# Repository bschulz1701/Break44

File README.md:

# Break44
A collection of various breakout and other utility boards

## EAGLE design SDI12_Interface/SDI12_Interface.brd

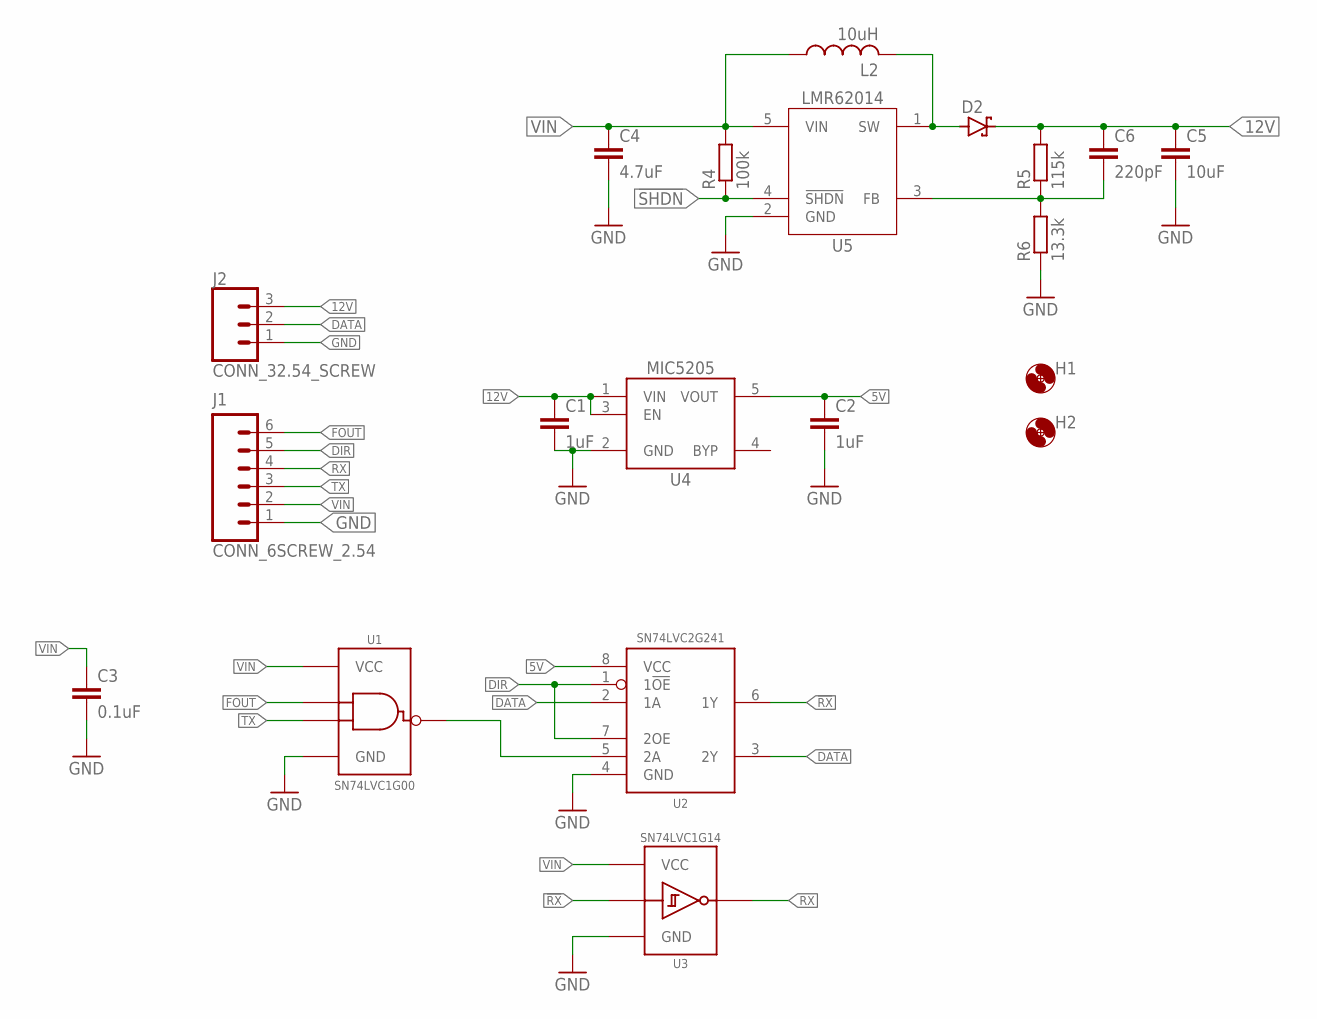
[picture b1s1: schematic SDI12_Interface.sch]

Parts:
C1, C2: 1uF; C0603
C3: 0.1uF; C0603
C4: 4.7uF; C0805
C5: 10uF; C0805; MPN TMK212BBJ106KG-T; DIGIKEY 587-2985-1-ND
C6: 220pF; C0603
D2: DIODE_SCHOTTKYSOD-123; SOD-123; MPN MBR0520LT1G; DIGIKEY MBR0520LT1GOSCT-ND
H1, H2: MOUNTING_HOLE2_NP; 2_56
J1: CONN_6SCREW_2.54; 1X06_SCREW
J2: CONN_32.54_SCREW; 1X03_SCREW
L2: 10uH; 1008; MPN 74438323100; DIGIKEY 732-4851-1-ND
R4: 100k; R0603
R5: 115k; R0603
R6: 13.3k; R0603
U1: SN74LVC1G00SC70; DCK_R-PDSO-G5
U2: SN74LVC2G241DCU; DCU_(R-PDSO-G8)
U3: SN74LVC1G14DCK; DCK_R-PDSO-G5
U4: MIC5205_5V; SOT23-5
U5: LMR62014SOT23; DBV0005A

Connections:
5V: C2.1, U2.8 (VCC), U4.5 (VOUT)
12V: C1.1, C5.1, C6.1, D2.CAT (C), J2.3, R5.2, U4.1 (VIN), U4.3 (EN)
!RX: U2.6 (1Y), U3.2 (A)
!SHDN: R4.1, U5.4 (!SHDN)
BYP: U4.4 (BYP)
DATA: J2.2, U2.2 (1A), U2.3 (2Y)
DIR: J1.5, U2.1 (1!OE), U2.7 (2OE)
FOUT: J1.6, U1.1 (A)
GND: C1.2, C2.2, C3.2, C4.2, C5.2, J1.1, J2.1, R6.1, U1.3 (GND), U2.4 (GND), U3.3 (GND), U4.2 (GND), U5.2 (GND)
unnamed: U1.4 (Y), U2.5 (2A)
unnamed: C6.2, R5.1, R6.2, U5.3 (FB)
RX: J1.4, U3.4 (Y)
SW1: D2.ANODE (A), L2.2, U5.1 (SW)
TX: J1.3, U1.2 (B)
VIN: C3.1, C4.1, J1.2, L2.1, R4.2, U1.5 (VCC), U3.5 (VCC), U5.5 (VIN)

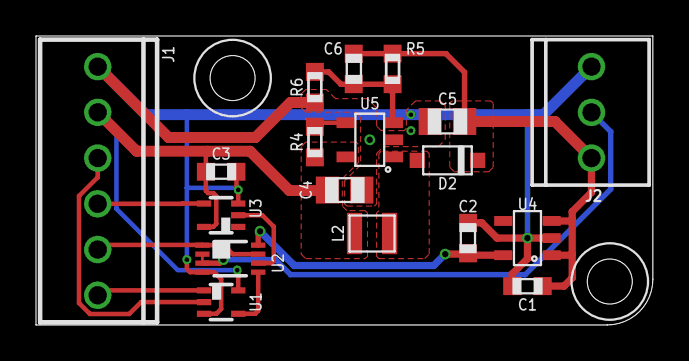
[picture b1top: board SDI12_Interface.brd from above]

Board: 2 copper layers, 34.3 x 16.1 mm, 20 parts (0 on the bottom side), 14 nets.

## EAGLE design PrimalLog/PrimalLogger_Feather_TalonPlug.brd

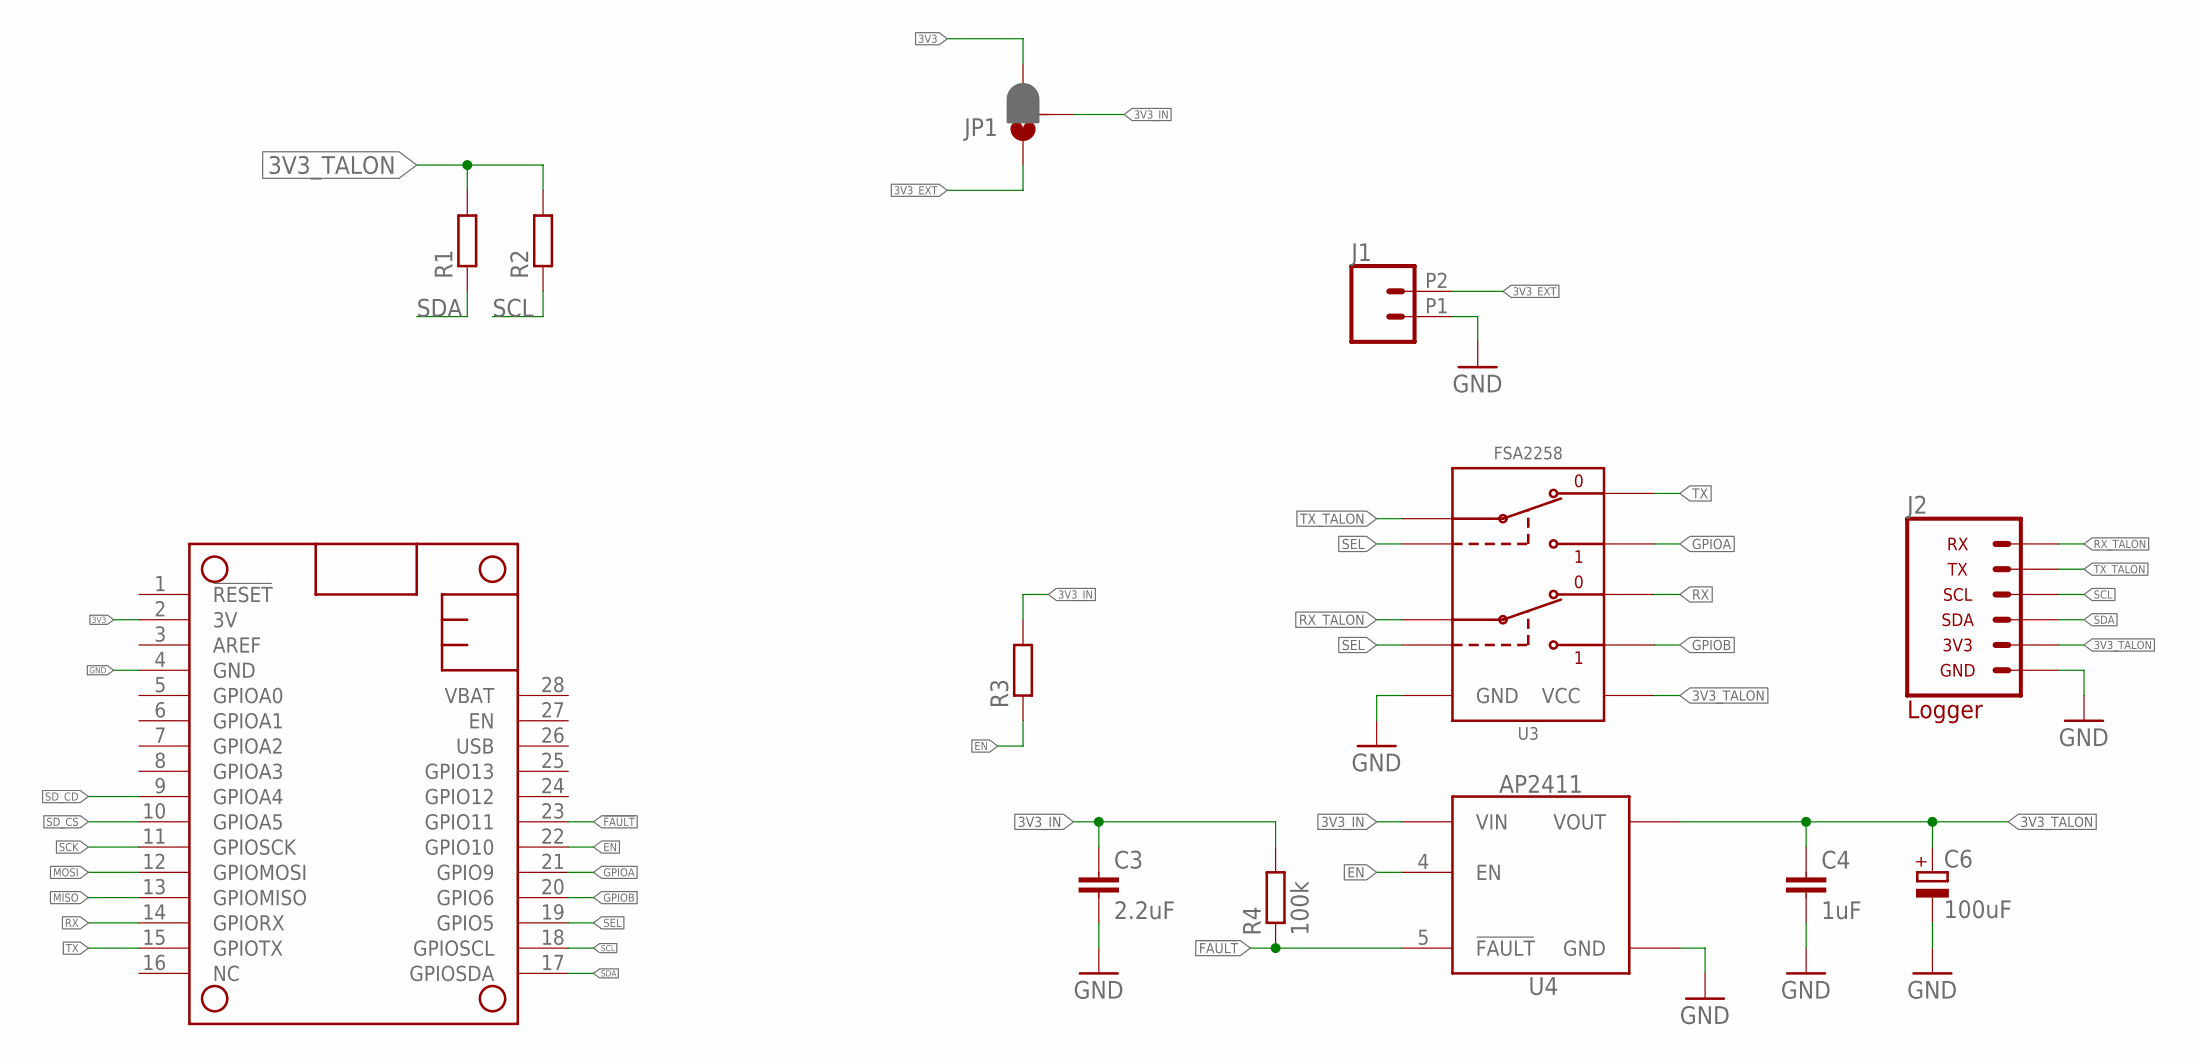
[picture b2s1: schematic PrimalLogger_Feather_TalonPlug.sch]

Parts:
C3: 2.2uF; C0603
C4: 1uF; C0603
C6: 100uF; C1411_TANT; MPN TPSB107M010R0400; DIGIKEY 478-5231-1-ND
J1: CONN_022.54_SCREW_ROUND; 1X02_2.54_SCREWTERM_ROUND
J2: CONN_TALON_LOGGER; 1X06_MICROLOCKPLUS_RT
JP1: JUMPER-SMT_3_1-NC_PASTE_SILK; SMT-JUMPER_3_1-NC_PASTE_SILK
MS1: FEATHERWING_NODIM; FEATHERWING_DIM
R1, R2: R-EU_10KR0603; R0603
R3: R-EU_100KR0603; R0603
R4: 100k; R0603
U3: FSA2258; MICROPAK_10
U4: AP2411; MSOP_8EP

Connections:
3V3: JP1.3, MS1.2 (3V)
3V3_EXT: J1.P2 (2), JP1.1
3V3_IN: C3.1, JP1.2, R3.2, R4.2, U4.2 (VIN), U4.3 (VIN)
3V3_TALON: C4.1, C6.ANODE (+), J2.2 (3V3), R1.2, R2.2, U3.10 (VCC), U4.6 (VOUT), U4.7 (VOUT)
!FAULT: MS1.23 (GPIO11), R4.1, U4.5 (!FAULT)
EN: MS1.22 (GPIO10), R3.1, U4.4 (EN)
GND: C3.2, C4.2, C6.CATHODE (-), J1.P1 (1), J2.1 (GND), MS1.4 (GND), U3.5 (GND), U4.1 (GND), U4.EP (GND)
GPIOA: MS1.21 (GPIO9), U3.2 (1B1)
GPIOB: MS1.20 (GPIO6), U3.4 (2B1)
MISO: MS1.13 (GPIOMISO)
MOSI: MS1.12 (GPIOMOSI)
RX: MS1.14 (GPIORX), U3.3 (2B0)
RX_TALON: J2.6 (RX), U3.6 (2A)
SCK: MS1.11 (GPIOSCK)
SCL: J2.4 (SCL), MS1.18 (GPIOSCL), R2.1
SDA: J2.3 (SDA), MS1.17 (GPIOSDA), R1.1
SD_CD: MS1.9 (GPIOA4)
SD_CS: MS1.10 (GPIOA5)
SEL: MS1.19 (GPIO5), U3.7 (S2), U3.8 (S1)
TX: MS1.15 (GPIOTX), U3.1 (1B0)
TX_TALON: J2.5 (TX), U3.9 (1A)

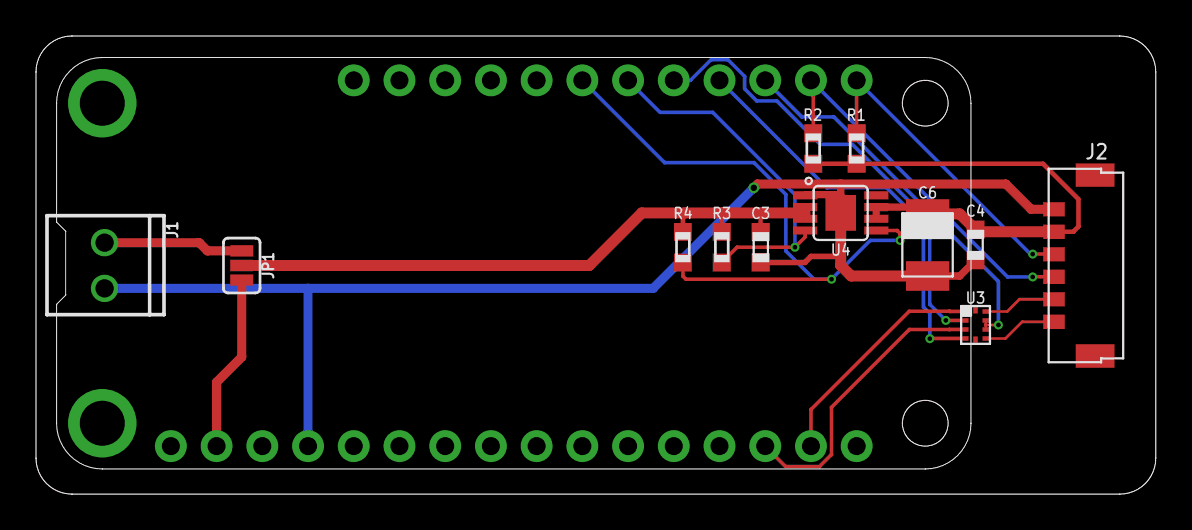
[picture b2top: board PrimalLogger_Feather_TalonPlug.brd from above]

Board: 2 copper layers, 62.2 x 25.5 mm, 13 parts (0 on the bottom side), 16 nets.

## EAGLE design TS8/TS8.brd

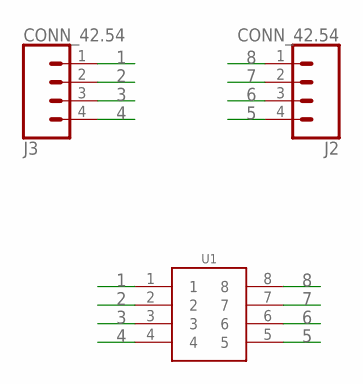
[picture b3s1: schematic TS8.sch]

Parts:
J2, J3: CONN_42.54; 1X04
U1: GEN_8TS8; TS8

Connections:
1: J3.1, U1.1
2: J3.2, U1.2
3: J3.3, U1.3
4: J3.4, U1.4
5: J2.4, U1.5
6: J2.3, U1.6
7: J2.2, U1.7
8: J2.1, U1.8

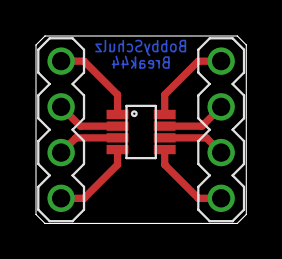
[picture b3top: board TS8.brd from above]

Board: 2 copper layers, 11.7 x 10.4 mm, 3 parts (0 on the bottom side), 8 nets.

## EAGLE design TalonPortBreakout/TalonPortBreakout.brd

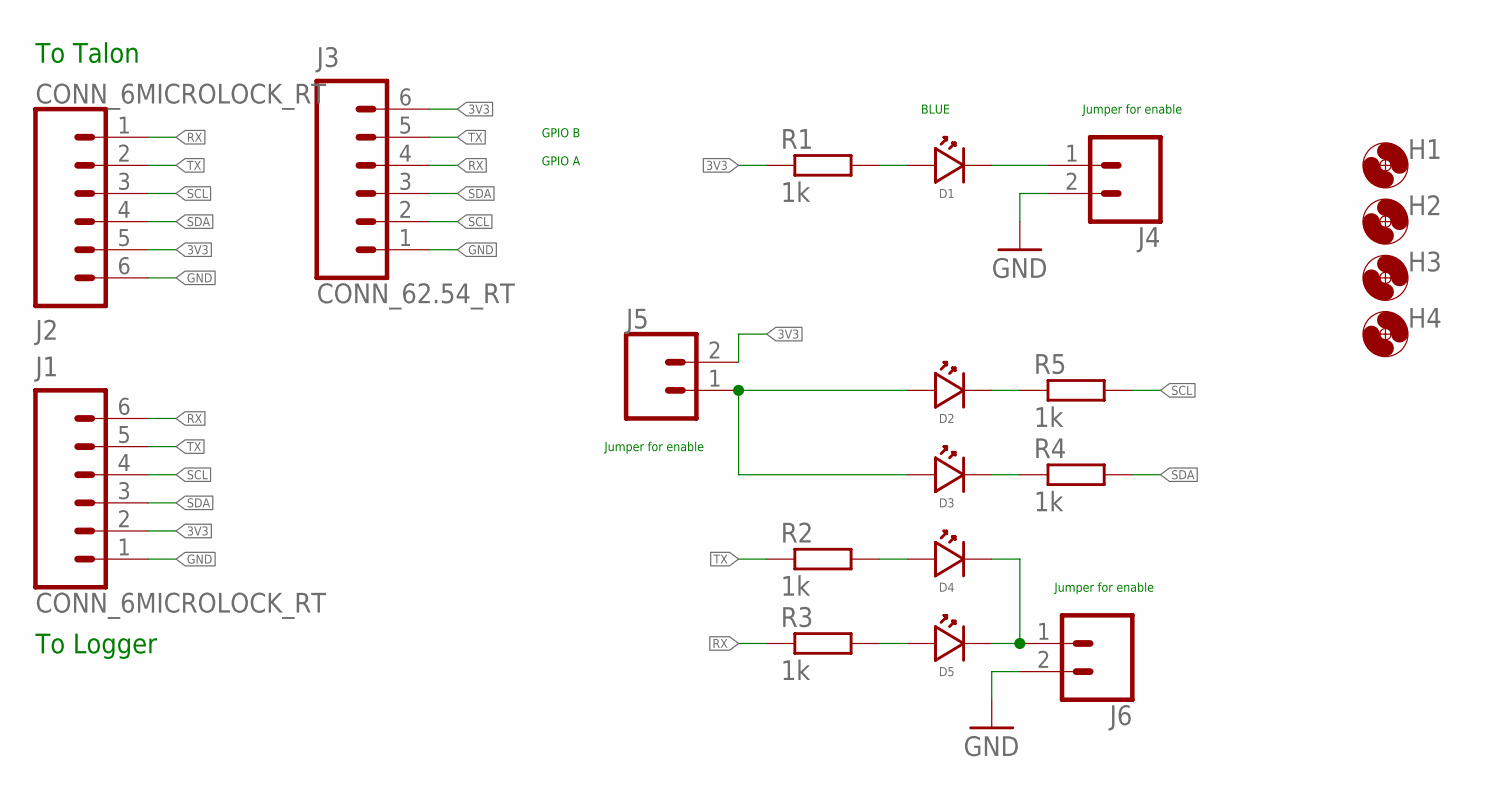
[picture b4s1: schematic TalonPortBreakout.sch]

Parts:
D1: LEDBLUE0603; LED_0603
D2, D3: LEDAMBER0603; LED_0603
D4: LEDGREEN0603; LED_0603
D5: LEDRED0603; LED_0603
H1, H2, H3, H4: MOUNTING_HOLE2_NP; 2_56
J1, J2: CONN_6MICROLOCK_RT; 1X06_MICROLOCKPLUS_RT
J3: CONN_62.54_RT; 1X06/90
J4, J5, J6: CONN_02; 1X02
R1, R2, R3, R4, R5: 1k; R0402

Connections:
3V3: J1.2, J2.5, J3.6, J5.2, R1.1
GND: J1.1, J2.6, J3.1, J4.2, J6.2
unnamed: D1.ANODE, R1.2
unnamed: D1.CATHODE, J4.1
unnamed: D4.ANODE, R2.2
unnamed: D5.ANODE, R3.2
unnamed: D3.CATHODE, R4.1
unnamed: D2.CATHODE, R5.1
unnamed: D4.CATHODE, D5.CATHODE, J6.1
unnamed: D2.ANODE, D3.ANODE, J5.1
RX: J1.6, J2.1, J3.4, R3.1
SCL: J1.4, J2.3, J3.2, R5.2
SDA: J1.3, J2.4, J3.3, R4.2
TX: J1.5, J2.2, J3.5, R2.1

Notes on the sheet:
GPIO B
GPIO A
BLUE
Jumper for enable
To Talon
To Logger

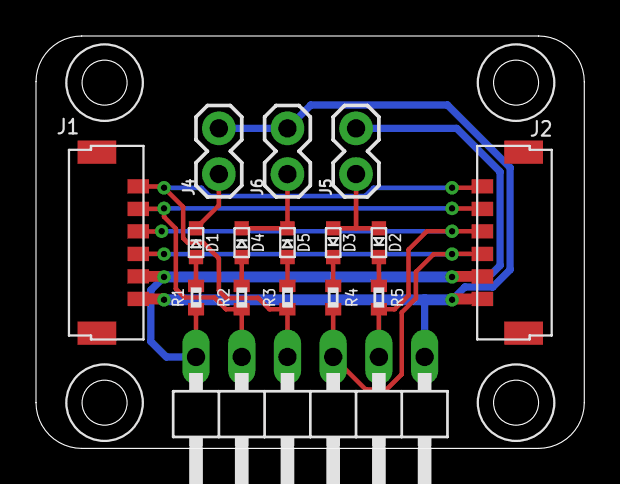
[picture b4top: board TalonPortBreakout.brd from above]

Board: 2 copper layers, 30.5 x 22.9 mm, 20 parts (0 on the bottom side), 14 nets.

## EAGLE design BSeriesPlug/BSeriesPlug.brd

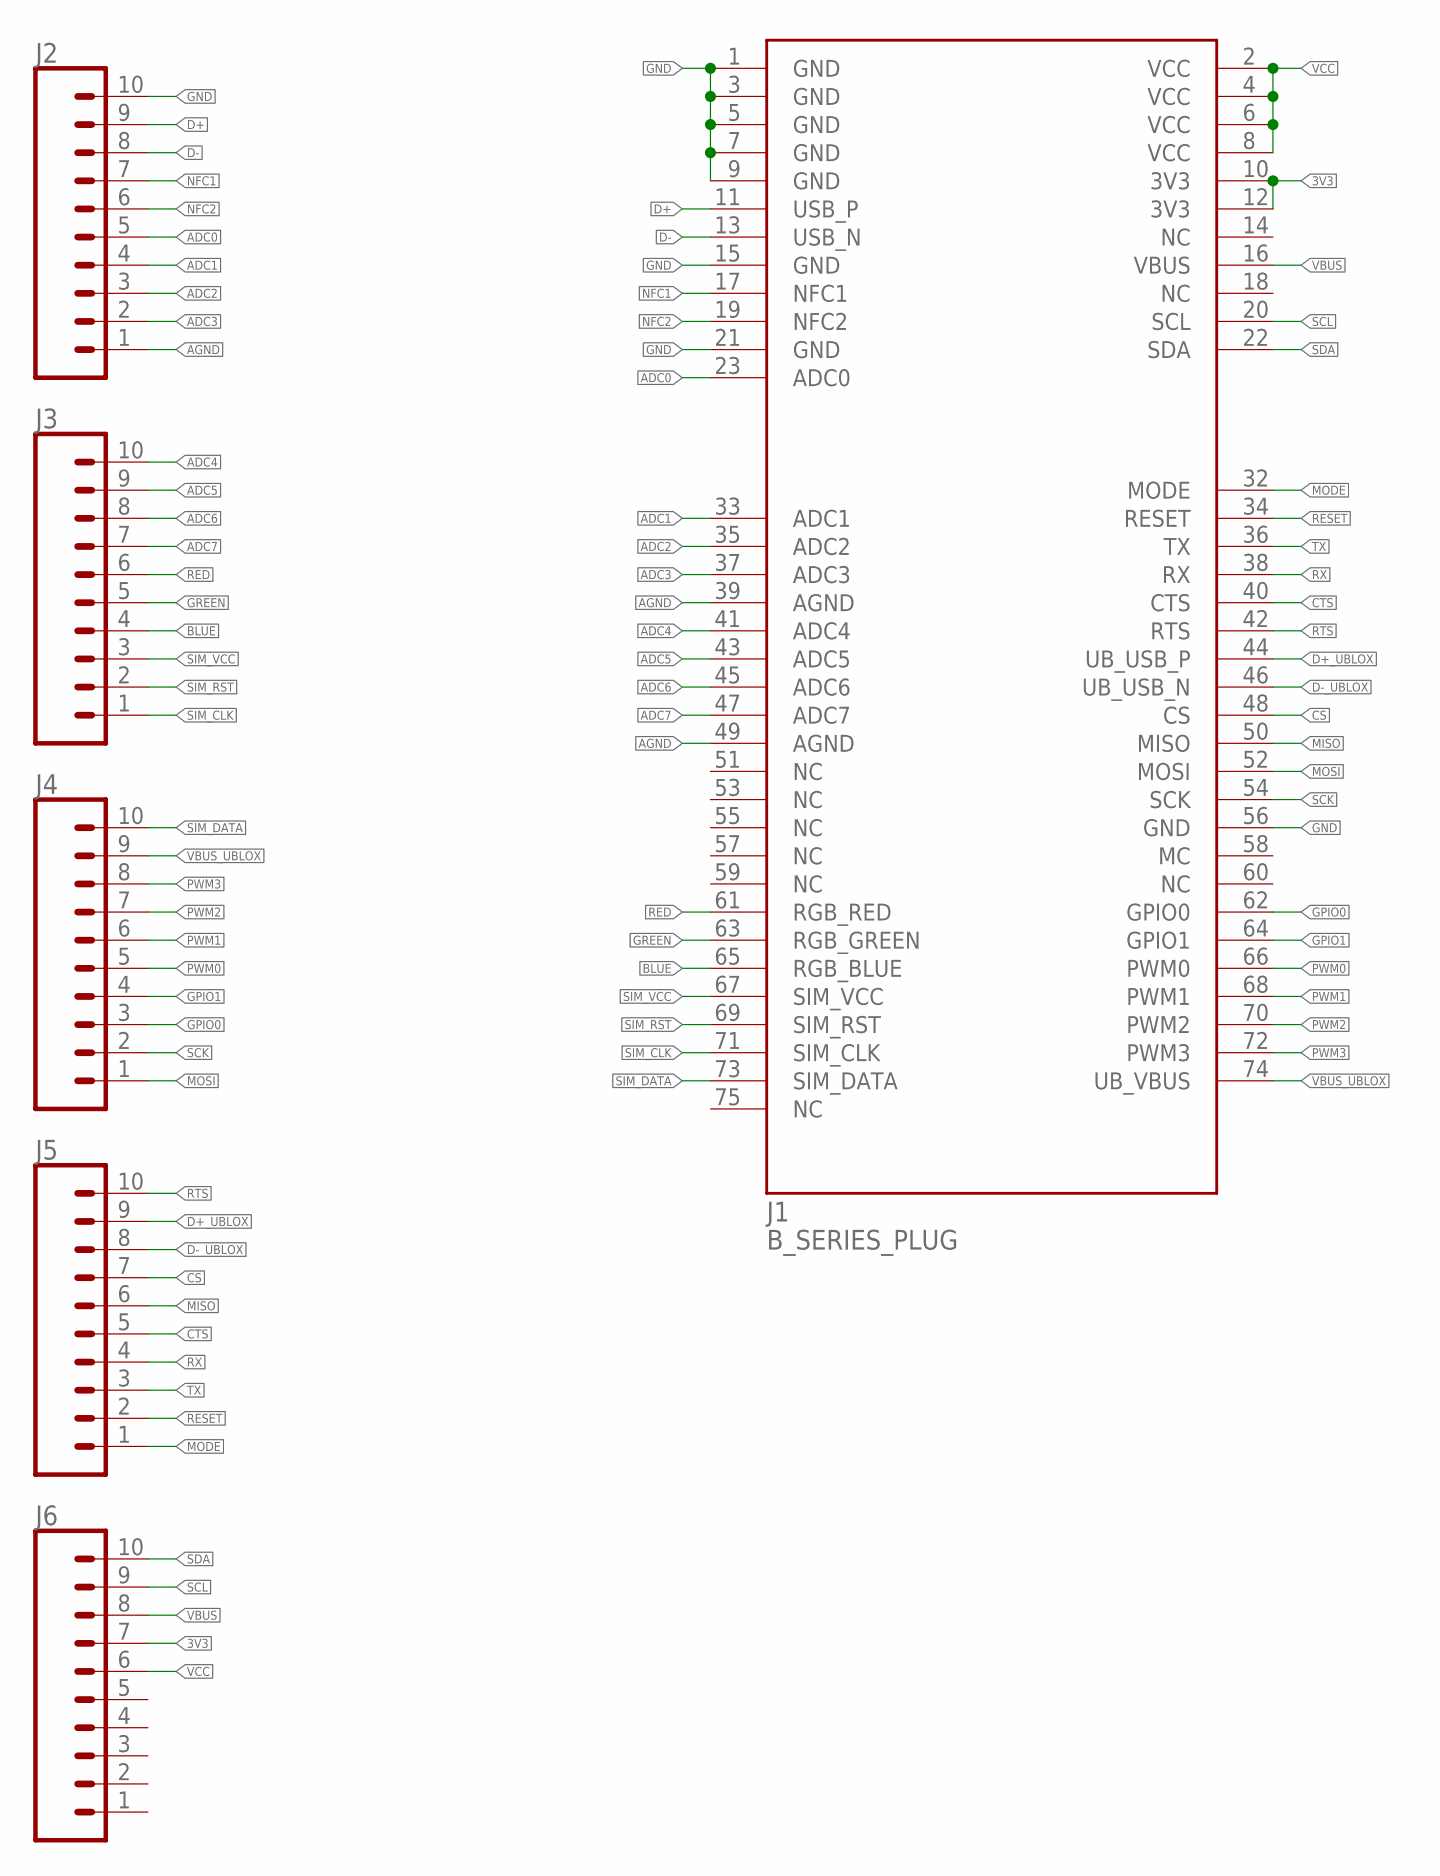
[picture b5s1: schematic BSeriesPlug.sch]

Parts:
J1: B_SERIES_PLUG; M.2-CARD-E-22
J2, J3, J4, J5, J6: CONN_10"; 1X10

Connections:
3V3: J1.10 (3V3), J1.12 (3V3), J6.7
ADC0: J1.23 (ADC0), J2.5
ADC1: J1.33 (ADC1), J2.4
ADC2: J1.35 (ADC2), J2.3
ADC3: J1.37 (ADC3), J2.2
ADC4: J1.41 (ADC4), J3.10
ADC5: J1.43 (ADC5), J3.9
ADC6: J1.45 (ADC6), J3.8
ADC7: J1.47 (ADC7), J3.7
AGND: J1.39 (AGND), J1.49 (AGND), J2.1
BLUE: J1.65 (RGB_BLUE), J3.4
CS: J1.48 (CS), J5.7
CTS: J1.40 (CTS), J5.5
D+: J1.11 (USB_P), J2.9
D+_UBLOX: J1.44 (UB_USB_P), J5.9
D-: J1.13 (USB_N), J2.8
D-_UBLOX: J1.46 (UB_USB_N), J5.8
GND: J1.1 (GND), J1.3 (GND), J1.5 (GND), J1.7 (GND), J1.9 (GND), J1.15 (GND), J1.21 (GND), J1.56 (GND), J2.10
GPIO0: J1.62 (GPIO0), J4.3
GPIO1: J1.64 (GPIO1), J4.4
GREEN: J1.63 (RGB_GREEN), J3.5
MISO: J1.50 (MISO), J5.6
MODE: J1.32 (MODE), J5.1
MOSI: J1.52 (MOSI), J4.1
NFC1: J1.17 (NFC1), J2.7
NFC2: J1.19 (NFC2), J2.6
PWM0: J1.66 (PWM0), J4.5
PWM1: J1.68 (PWM1), J4.6
PWM2: J1.70 (PWM2), J4.7
PWM3: J1.72 (PWM3), J4.8
RED: J1.61 (RGB_RED), J3.6
RESET: J1.34 (RESET), J5.2
RTS: J1.42 (RTS), J5.10
RX: J1.38 (RX), J5.4
SCK: J1.54 (SCK), J4.2
SCL: J1.20 (SCL), J6.9
SDA: J1.22 (SDA), J6.10
SIM_CLK: J1.71 (SIM_CLK), J3.1
SIM_DATA: J1.73 (SIM_DATA), J4.10
SIM_RST: J1.69 (SIM_RST), J3.2
SIM_VCC: J1.67 (SIM_VCC), J3.3
TX: J1.36 (TX), J5.3
VBUS: J1.16 (VBUS), J6.8
VBUS_UBLOX: J1.74 (UB_VBUS), J4.9
VCC: J1.2 (VCC), J1.4 (VCC), J1.6 (VCC), J1.8 (VCC), J6.6

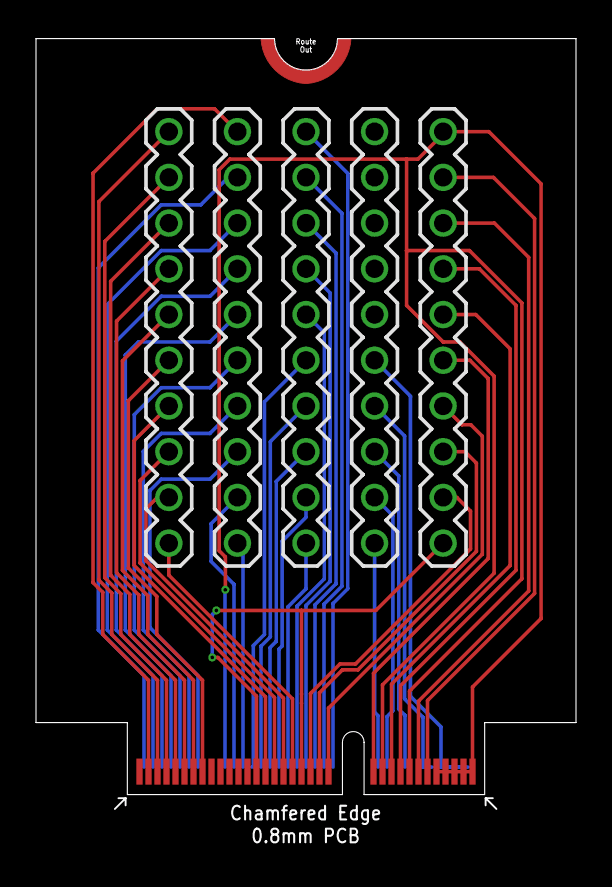
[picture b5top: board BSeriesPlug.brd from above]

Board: 2 copper layers, 29.9 x 45.2 mm, 6 parts (0 on the bottom side), 45 nets.

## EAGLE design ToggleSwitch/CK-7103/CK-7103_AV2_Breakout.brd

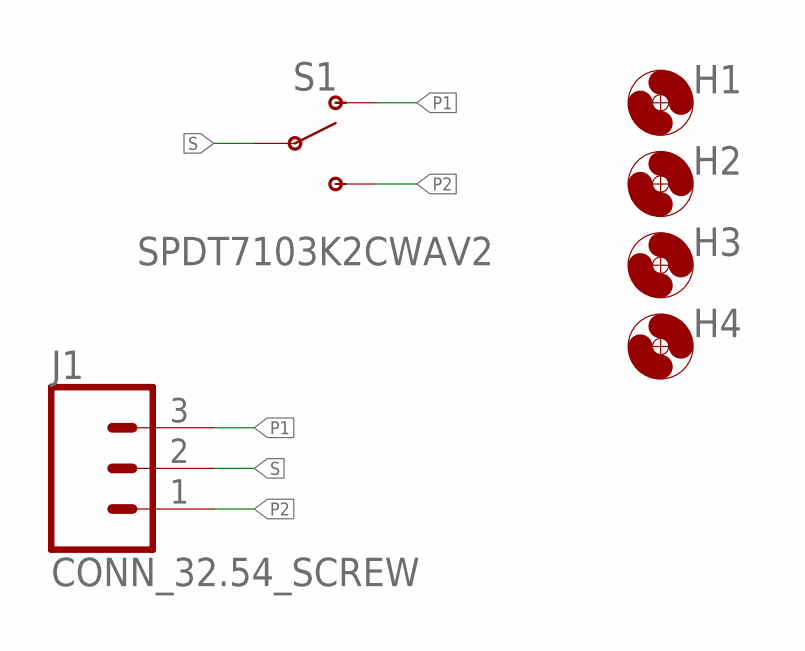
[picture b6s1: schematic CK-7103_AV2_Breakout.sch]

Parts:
H1, H2, H3, H4: MOUNTING_HOLE4_NP; 4_40
J1: CONN_32.54_SCREW; 1X03_SCREW
S1: SPDT7103K2CWAV2; 7103K2CWAV2

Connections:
P1: J1.3, S1.1 (O)
P2: J1.1, S1.3 (S)
S: J1.2, S1.2

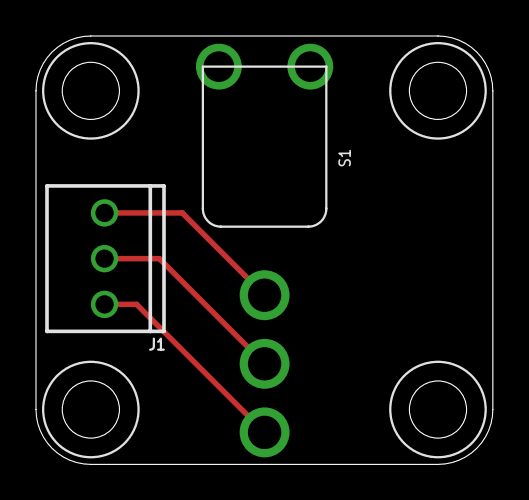
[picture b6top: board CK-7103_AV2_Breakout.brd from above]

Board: 2 copper layers, 25.4 x 23.8 mm, 6 parts (0 on the bottom side), 3 nets.

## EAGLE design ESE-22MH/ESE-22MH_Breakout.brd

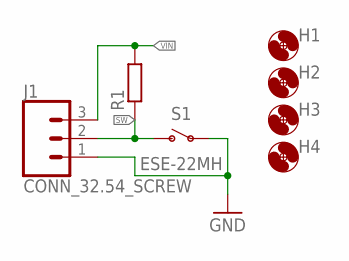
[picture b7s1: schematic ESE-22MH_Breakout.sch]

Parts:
H1, H2, H3, H4: MOUNTING_HOLE4_NP; 4_40
J1: CONN_32.54_SCREW; 1X03_SCREW
R1: R-EU_R0603; R0603
S1: ESE-22MH

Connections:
GND: J1.1, S1.2
SW: J1.2, R1.1, S1.1 (O)
VIN: J1.3, R1.2

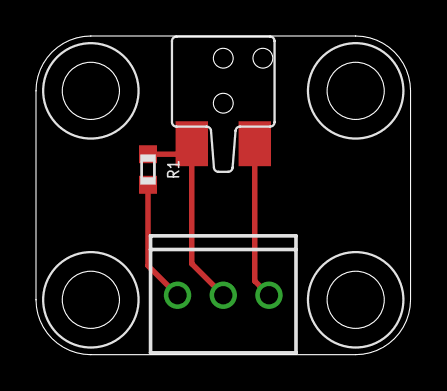
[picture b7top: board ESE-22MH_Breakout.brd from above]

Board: 2 copper layers, 20.8 x 17.7 mm, 7 parts (0 on the bottom side), 3 nets.

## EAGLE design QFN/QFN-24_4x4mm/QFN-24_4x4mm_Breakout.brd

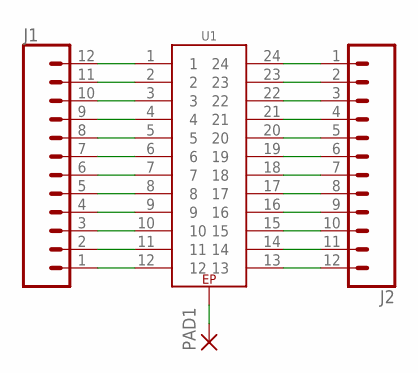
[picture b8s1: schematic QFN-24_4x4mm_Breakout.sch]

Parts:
J1, J2: CONN_12; 1X12
PAD1: SMD2; SMD1,27-2,54
U1: GEN_24_EPQFN-24; QFN24

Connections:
unnamed: PAD1.1, U1.EP
unnamed: J1.12, U1.1
unnamed: J1.11, U1.2
unnamed: J1.10, U1.3
unnamed: J1.9, U1.4
unnamed: J1.8, U1.5
unnamed: J1.7, U1.6
unnamed: J1.6, U1.7
unnamed: J1.5, U1.8
unnamed: J1.4, U1.9
unnamed: J1.3, U1.10
unnamed: J1.2, U1.11
unnamed: J1.1, U1.12
unnamed: J2.12, U1.13
unnamed: J2.11, U1.14
unnamed: J2.10, U1.15
unnamed: J2.9, U1.16
unnamed: J2.8, U1.17
unnamed: J2.7, U1.18
unnamed: J2.6, U1.19
unnamed: J2.5, U1.20
unnamed: J2.4, U1.21
unnamed: J2.3, U1.22
unnamed: J2.2, U1.23
unnamed: J2.1, U1.24

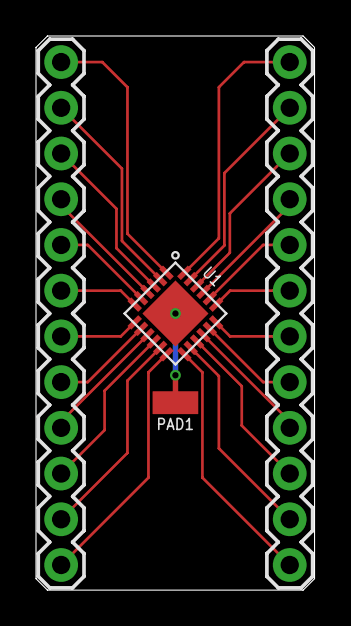
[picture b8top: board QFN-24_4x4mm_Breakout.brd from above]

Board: 2 copper layers, 15.5 x 30.8 mm, 4 parts (0 on the bottom side), 25 nets.

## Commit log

2019-04-12 Added LICENSE
2019-04-13 Added SC70/SOT23 breakout
2019-04-20 Added 8 pin multi breakout
    Added single breakout for DQM, DQE, and VSOP-8
2019-09-12 Added DPS368 Hardened Pressure Sensor Breakout
2019-09-12 Added MS5803 and MS5837 Pressure sensor breakouts
2020-02-22 Added PAC1720 Breakout
    Added current sense breakout
2020-03-14 Added PrimalLogger breakouts
    Added primal logger designs for photon and feather
2020-05-07 Added breakouts for passive SMD parts
    Added breakouts for 0402, 0603, 0805, 1206, 1210 SMD parts
2020-05-08 Updated passive SMD breakout boards to meet PCB specs
    JLC PCB requires a 5x5mm minimum size, and the single SMD adapters were too small for this, so converted to make them wide enough, and made them "dual" to maximize the spaced used
2020-08-26 Added feather, PAC1932 breakout
2020-08-26 Added LED breakout
2020-08-26 Added general reference card v0.0
2020-09-29 Fixed folder name to be Windows compatible
    Removed random character from `SMD_Passives` folder name
2020-10-30 Added MCP3421 ADC breakout
2020-12-18 Added SOIC/SSOP breakout board for 14 and 20 pin
    Added standard SOIC/SSOP breakout boards for 14 pin and 20 pin count, cleanup/checking required along with gerber generation
2020-12-19 Added battery charger and BMS eval boards
    Added eval board for the BQ25616 and BQ2980
2020-12-19 Added vertical SOT breakout and USB breakout
    Added vertical SOT breakout for SMD transistor breadboarding in a compact way. Added waterproof USB breakout, need to test success of milling in gerbers
2020-12-19 Gerbers for SOIC/SSOP generic breakouts
2021-03-04 Added tactile switch breakouts
    Added existing tactile switch breakouts
2021-03-04 Updated tactile switch combo resistor
    Changed the resistor layout on the combo switch breakout to be more relaxed and work more easily with standard 1/4 W resistors
2021-04-14 Added breadboard jumper
    Added jumper for breadboard power rails, design and gerbers. v0.0 sent to fab
2021-04-14 Initial dev for SD12 interface
    Development for SDI12 hardware UART interface. v0.0 sent to fab, very rapid development, schematic needs cleanup after the fact
2021-07-23 Updated part info for SDI12_Interface
2021-07-23 Added MicroLock connector breakout
2021-07-23 Added power module breakouts: PAM2320, TPS61022
    Added buck and boost power modules
    Note: Should these be moved to Tosche?
2021-07-24 Added light sensor breakouts
    Added VEML6030 and VEML7700 modules
2021-07-24 Updates to power modules
2021-07-24 Fix for breadboard jumper
2021-07-24 Added MAX-M8 GPS module/breakout
2021-07-24 Added Particle SoM breakout
2021-07-24 Added LGA, DFN, and others
    Added many individual breakouts for sensor testing and some power devices
2021-10-08 Added pas through micro lock connector breakout
2021-10-08 Added 10 pin SOIC/SSOP
2021-10-08 Fixed spacing on SOIC/SSOP 14 breakout
2021-10-08 Updated MAX-M8 breakout with active antenna support
2021-10-12 Added DFN and MicroPak breakouts
    Added breakouts for DFN 8 and MicroPak 10
2021-10-12 Added multiple QFN breakouts (8, 16, 20, 24)
2021-10-12 Added switch breakouts
    Added breakouts for 7000 series right angle switch and ESE-22MH limit switch
2021-10-12 Added rechargeable coin cell breakout
    Added breakout for ML612S lithium coin cell breakout
2021-10-12 Added WSON-8 breakout
2021-10-14 Generated gerbers for QFN8 and WSON8
2021-10-14 Renamed C&K switch
    Changed name of C&K switch to CK since JLCPCB was not happy with special characters in file names
2021-10-14 Added breakout for AV2 model 7103 switch
    Added breakout for vertical switch model
2024-08-01 Fixed inverter in SDI-12 interface
    SDI-12 interface erroneously had non-inverting buffer instead of inverting buffer
2024-10-11 Backlog of various boards
2024-10-11 Fixed board<->schematic consistency in PrimalLog TalonPlug
2024-10-11 SDI12 Interface somehow disappeared - fixed
